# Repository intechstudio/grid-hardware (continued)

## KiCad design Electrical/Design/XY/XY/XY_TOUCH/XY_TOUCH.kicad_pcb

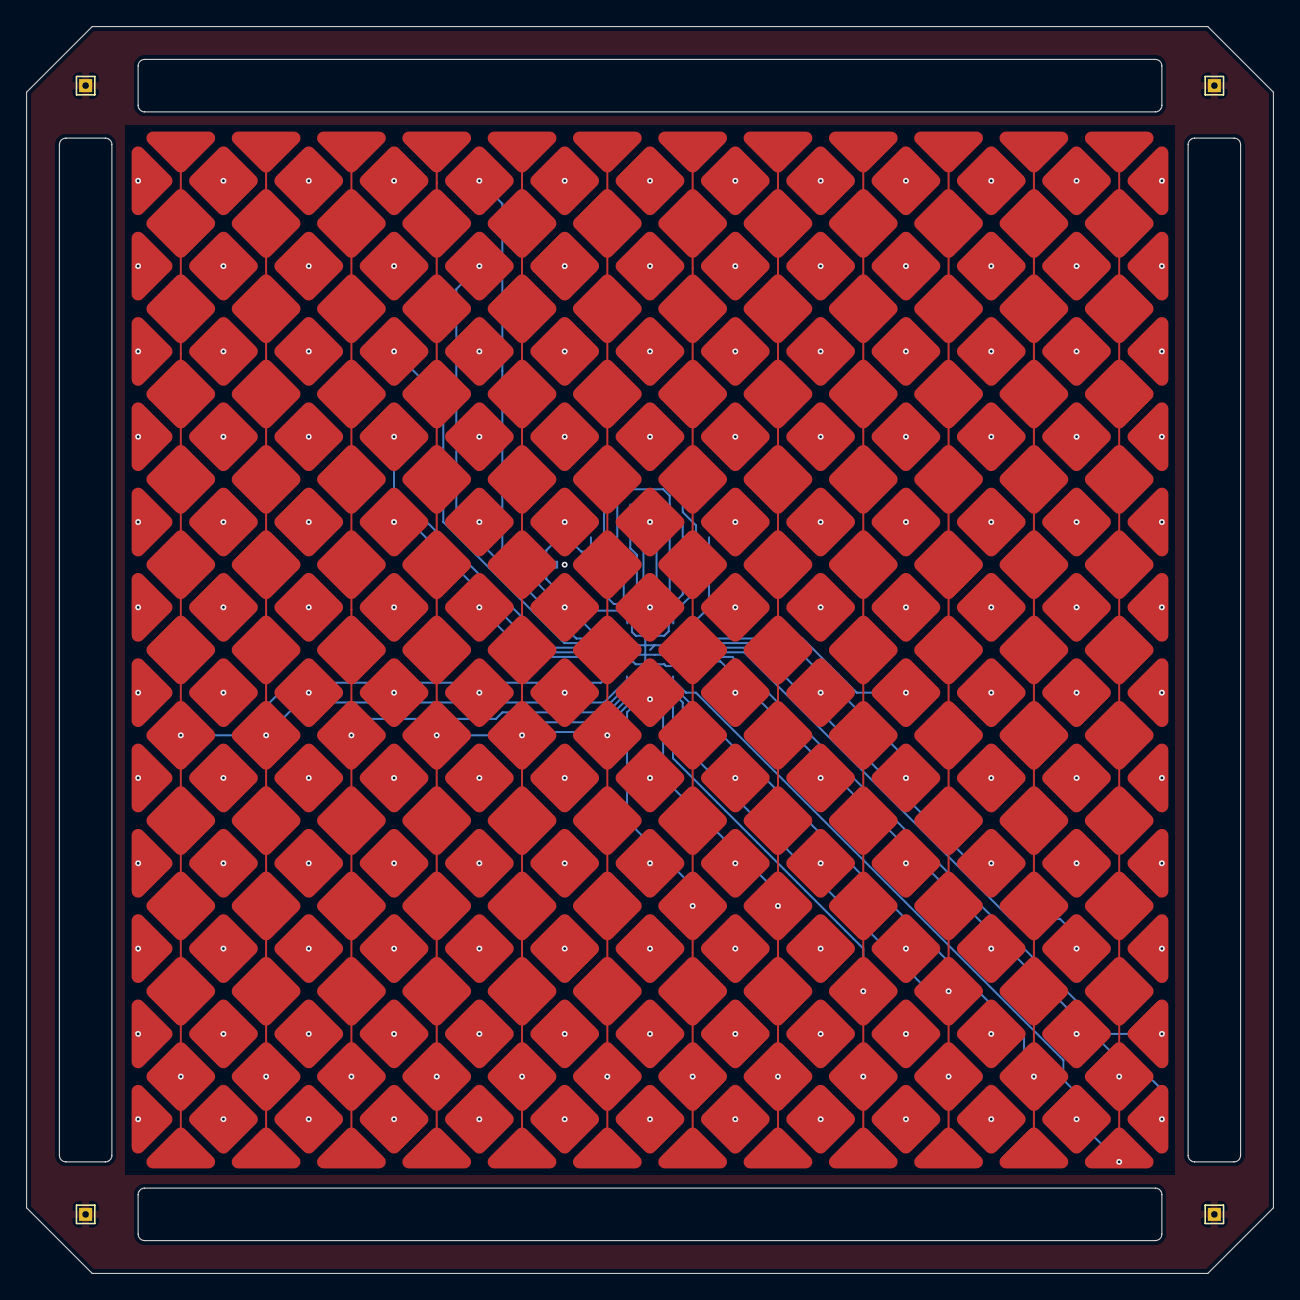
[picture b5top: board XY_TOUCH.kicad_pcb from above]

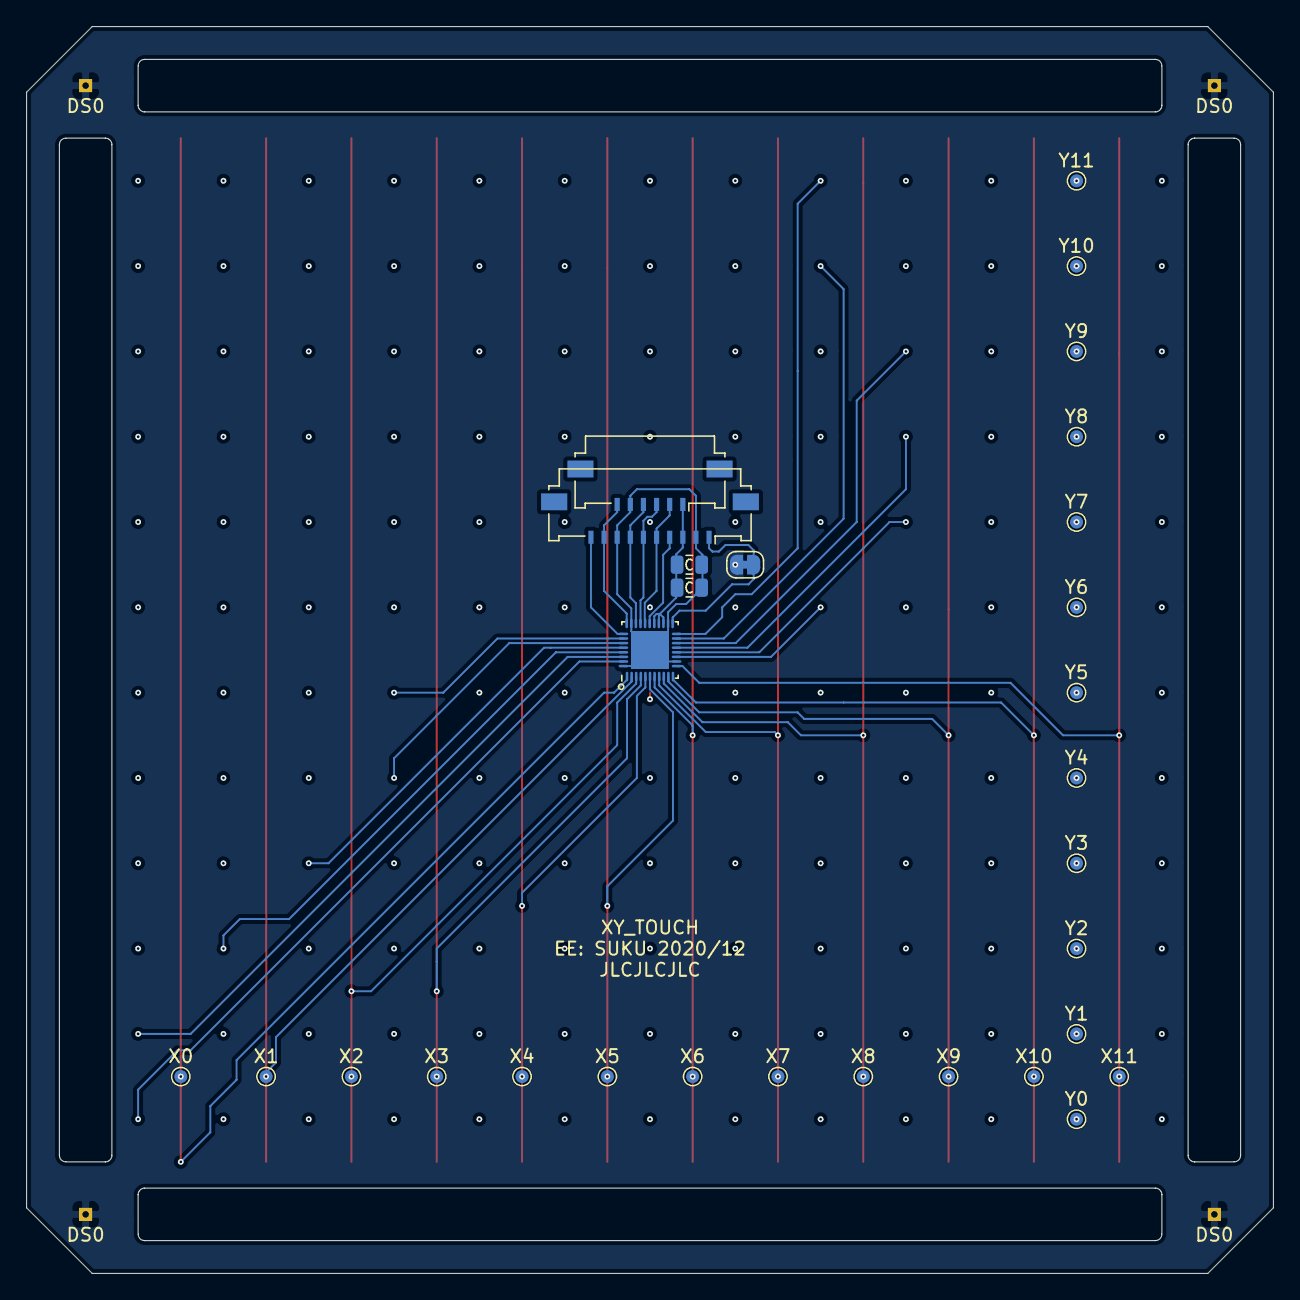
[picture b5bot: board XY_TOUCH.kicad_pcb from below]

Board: 4 copper layers, 95.0 x 95.0 mm, 346 parts (30 on the bottom side), 34 nets.

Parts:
C1: 100n; CAP_0805
C2: 1u; CAP_0805
CS1, CS2, CS3, CS4, CS5, CS6, CS7, CS8, CS9, CS10, CS11, CS12, CS13, CS25, CS38, CS50, CS63, CS75, CS88, CS100, CS113, CS125, CS138, CS150, CS163, CS175, CS188, CS200, CS213, CS225, CS238, CS250, CS263, CS275, CS288, CS300, CS301, CS302, CS303, CS304, CS305, CS306, CS307, CS308, CS309, CS310, CS311, CS312: capsense_diamond_edge
CS14, CS15, CS16, CS17, CS18, CS19, CS20, CS21, CS22, CS23, CS24, CS26, CS27, CS28, CS29, CS30, CS31, CS32, CS33, CS34, CS35, CS36, CS37, CS39, CS40, CS41, CS42, CS43, CS44, CS45, CS46, CS47, CS48, CS49, CS51, CS52, CS53, CS54, CS55, CS56, CS57, CS58, CS59, CS60, CS61, CS62, CS64, CS65, CS66, CS67, CS68, CS69, CS70, CS71, CS72, CS73, CS74, CS76, CS77, CS78, CS79, CS80, CS81, CS82, CS83, CS84, CS85, CS86, CS87, CS89, CS90, CS91, CS92, CS93, CS94, CS95, CS96, CS97, CS98, CS99, CS101, CS102, CS103, CS104, CS105, CS106, CS107, CS108, CS109, CS110, CS111, CS112, CS114, CS115, CS116, CS117, CS118, CS119, CS120, CS121, CS122, CS123, CS124, CS126, CS127, CS128, CS129, CS130, CS131, CS132, CS133, CS134, CS135, CS136, CS137, CS139, CS140, CS141, CS142, CS143, CS144, CS145, CS146, CS147, CS148, CS149, CS151, CS152, CS153, CS154, CS155, CS156, CS157, CS158, CS159, CS160, CS161, CS162, CS164, CS165, CS166, CS167, CS168, CS169, CS170, CS171, CS172, CS173, CS174, CS176, CS177, CS178, CS179, CS180, CS181, CS182, CS183, CS184, CS185, CS186, CS187, CS189, CS190, CS191, CS192, CS193, CS194, CS195, CS196, CS197, CS198, CS199, CS201, CS202, CS203, CS204, CS205, CS206, CS207, CS208, CS209, CS210, CS211, CS212, CS214, CS215, CS216, CS217, CS218, CS219, CS220, CS221, CS222, CS223, CS224, CS226, CS227, CS228, CS229, CS230, CS231, CS232, CS233, CS234, CS235, CS236, CS237, CS239, CS240, CS241, CS242, CS243, CS244, CS245, CS246, CS247, CS248, CS249, CS251, CS252, CS253, CS254, CS255, CS256, CS257, CS258, CS259, CS260, CS261, CS262, CS264, CS265, CS266, CS267, CS268, CS269, CS270, CS271, CS272, CS273, CS274, CS276, CS277, CS278, CS279, CS280, CS281, CS282, CS283, CS284, CS285, CS286, CS287, CS289, CS290, CS291, CS292, CS293, CS294, CS295, CS296, CS297, CS298, CS299: capsense_diamond
J1: Conn_01x06; Molex_200528-0060_1x06-1MP_P1.00mm_Horizontal
J2: Conn_01x10; Molex_200528-0100_1x10-1MP_P1.00mm_Horizontal
JP1: Jumper_2_Bridged; SolderJumper-2_P1.3mm_Bridged_RoundedPad1.0x1.5mm
TP1, TP2, TP3, TP4: DS0; TestPoint_THTPad_1.0x1.0mm_Drill0.5mm
TP5: X11; TestPoint_Pad_D1.0mm
TP6: X10; TestPoint_Pad_D1.0mm
TP7: X9; TestPoint_Pad_D1.0mm
TP8: X8; TestPoint_Pad_D1.0mm
TP9: X7; TestPoint_Pad_D1.0mm
TP10: X6; TestPoint_Pad_D1.0mm
TP11: X5; TestPoint_Pad_D1.0mm
TP12: X4; TestPoint_Pad_D1.0mm
TP13: X3; TestPoint_Pad_D1.0mm
TP14: X2; TestPoint_Pad_D1.0mm
TP15: X1; TestPoint_Pad_D1.0mm
TP16: X0; TestPoint_Pad_D1.0mm
TP17: Y11; TestPoint_Pad_D1.0mm
TP18: Y10; TestPoint_Pad_D1.0mm
TP19: Y9; TestPoint_Pad_D1.0mm
TP20: Y8; TestPoint_Pad_D1.0mm
TP21: Y7; TestPoint_Pad_D1.0mm
TP22: Y6; TestPoint_Pad_D1.0mm
TP23: Y5; TestPoint_Pad_D1.0mm
TP24: Y4; TestPoint_Pad_D1.0mm
TP25: Y3; TestPoint_Pad_D1.0mm
TP26: Y2; TestPoint_Pad_D1.0mm
TP27: Y1; TestPoint_Pad_D1.0mm
TP28: Y0; TestPoint_Pad_D1.0mm
U1: MXT144U; QFN-38_EP_4x4_Pitch0.35mm

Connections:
+3V3_UI: C1.1, C2.1, J1.1, J2.3, U1.22, U1.23, U1.24
/CHG: J1.6, J2.9, U1.30
/DBG_CLK: J2.4, U1.25
/DBG_DATA: J2.1, JP1.2, U1.20
/DBG_SS: J2.10, U1.31
/DS0: JP1.1, TP1.1, TP2.1, TP3.1, TP4.1
/RESET: J1.4, J2.7, U1.28
/SCL: J1.3, J2.6, U1.27
/SDA: J1.2, J2.5, U1.26
/X0: CS288.1, CS289.1, CS290.1, CS291.1, CS292.1, CS293.1, CS294.1, CS295.1, CS296.1, CS297.1, CS298.1, CS299.1, CS300.1, TP16.1, U1.1
/X1: CS263.1, CS264.1, CS265.1, CS266.1, CS267.1, CS268.1, CS269.1, CS270.1, CS271.1, CS272.1, CS273.1, CS274.1, CS275.1, TP15.1, U1.2
/X2: CS238.1, CS239.1, CS240.1, CS241.1, CS242.1, CS243.1, CS244.1, CS245.1, CS246.1, CS247.1, CS248.1, CS249.1, CS250.1, TP14.1, U1.3
/X3: CS213.1, CS214.1, CS215.1, CS216.1, CS217.1, CS218.1, CS219.1, CS220.1, CS221.1, CS222.1, CS223.1, CS224.1, CS225.1, TP13.1, U1.4
/X4: CS188.1, CS189.1, CS190.1, CS191.1, CS192.1, CS193.1, CS194.1, CS195.1, CS196.1, CS197.1, CS198.1, CS199.1, CS200.1, TP12.1, U1.5
/X5: CS163.1, CS164.1, CS165.1, CS166.1, CS167.1, CS168.1, CS169.1, CS170.1, CS171.1, CS172.1, CS173.1, CS174.1, CS175.1, TP11.1, U1.6
/X6: CS138.1, CS139.1, CS140.1, CS141.1, CS142.1, CS143.1, CS144.1, CS145.1, CS146.1, CS147.1, CS148.1, CS149.1, CS150.1, TP10.1, U1.7
/X7: CS113.1, CS114.1, CS115.1, CS116.1, CS117.1, CS118.1, CS119.1, CS120.1, CS121.1, CS122.1, CS123.1, CS124.1, CS125.1, TP9.1, U1.8
/X8: CS88.1, CS89.1, CS90.1, CS91.1, CS92.1, CS93.1, CS94.1, CS95.1, CS96.1, CS97.1, CS98.1, CS99.1, CS100.1, TP8.1, U1.9
/X9: CS63.1, CS64.1, CS65.1, CS66.1, CS67.1, CS68.1, CS69.1, CS70.1, CS71.1, CS72.1, CS73.1, CS74.1, CS75.1, TP7.1, U1.10
/X10: CS38.1, CS39.1, CS40.1, CS41.1, CS42.1, CS43.1, CS44.1, CS45.1, CS46.1, CS47.1, CS48.1, CS49.1, CS50.1, TP6.1, U1.11
/X11: CS13.1, CS14.1, CS15.1, CS16.1, CS17.1, CS18.1, CS19.1, CS20.1, CS21.1, CS22.1, CS23.1, CS24.1, CS25.1, TP5.1, U1.12
/Y0: CS12.1, CS37.1, CS62.1, CS87.1, CS112.1, CS137.1, CS162.1, CS187.1, CS212.1, CS237.1, CS262.1, CS287.1, CS312.1, TP28.1, U1.37
/Y1: CS11.1, CS36.1, CS61.1, CS86.1, CS111.1, CS136.1, CS161.1, CS186.1, CS211.1, CS236.1, CS261.1, CS286.1, CS311.1, TP27.1, U1.36
/Y2: CS10.1, CS35.1, CS60.1, CS85.1, CS110.1, CS135.1, CS160.1, CS185.1, CS210.1, CS235.1, CS260.1, CS285.1, CS310.1, TP26.1, U1.35
/Y3: CS9.1, CS34.1, CS59.1, CS84.1, CS109.1, CS134.1, CS159.1, CS184.1, CS209.1, CS234.1, CS259.1, CS284.1, CS309.1, TP25.1, U1.34
/Y4: CS8.1, CS33.1, CS58.1, CS83.1, CS108.1, CS133.1, CS158.1, CS183.1, CS208.1, CS233.1, CS258.1, CS283.1, CS308.1, TP24.1, U1.33
/Y5: CS7.1, CS32.1, CS57.1, CS82.1, CS107.1, CS132.1, CS157.1, CS182.1, CS207.1, CS232.1, CS257.1, CS282.1, CS307.1, TP23.1, U1.32
/Y6: CS6.1, CS31.1, CS56.1, CS81.1, CS106.1, CS131.1, CS156.1, CS181.1, CS206.1, CS231.1, CS256.1, CS281.1, CS306.1, TP22.1, U1.14
/Y7: CS5.1, CS30.1, CS55.1, CS80.1, CS105.1, CS130.1, CS155.1, CS180.1, CS205.1, CS230.1, CS255.1, CS280.1, CS305.1, TP21.1, U1.15
/Y8: CS4.1, CS29.1, CS54.1, CS79.1, CS104.1, CS129.1, CS154.1, CS179.1, CS204.1, CS229.1, CS254.1, CS279.1, CS304.1, TP20.1, U1.16
/Y9: CS3.1, CS28.1, CS53.1, CS78.1, CS103.1, CS128.1, CS153.1, CS178.1, CS203.1, CS228.1, CS253.1, CS278.1, CS303.1, TP19.1, U1.17
/Y10: CS2.1, CS27.1, CS52.1, CS77.1, CS102.1, CS127.1, CS152.1, CS177.1, CS202.1, CS227.1, CS252.1, CS277.1, CS302.1, TP18.1, U1.18
/Y11: CS1.1, CS26.1, CS51.1, CS76.1, CS101.1, CS126.1, CS151.1, CS176.1, CS201.1, CS226.1, CS251.1, CS276.1, CS301.1, TP17.1, U1.19
GND: C1.2, C2.2, J1.5, J2.2, J2.8, U1.13, U1.21, U1.29, U1.38, U1.39

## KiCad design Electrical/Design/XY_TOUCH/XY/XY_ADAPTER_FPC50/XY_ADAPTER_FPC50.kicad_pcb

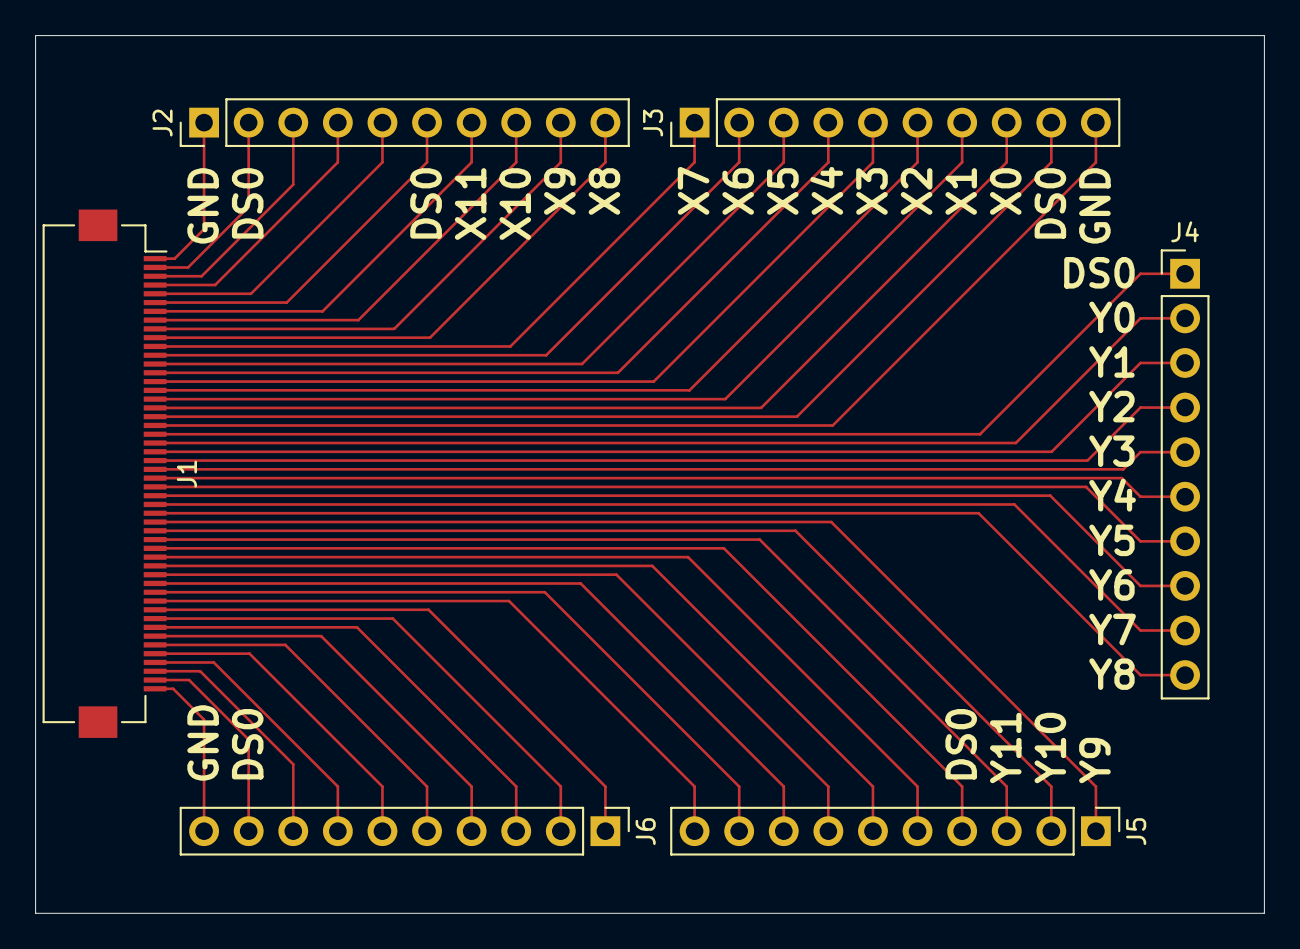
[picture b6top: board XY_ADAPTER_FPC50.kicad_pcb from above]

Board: 2 copper layers, 70.0 x 50.0 mm, 6 parts (0 on the bottom side), 50 nets.

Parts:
J1: Conn_01x50; Hirose_FH12-50S-0.5SH_1x50-1MP_P0.50mm_Horizontal
J2, J3, J4, J5, J6: Conn_01x10; PinHeader_1x10_P2.54mm_Vertical

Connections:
unnamed: J1.1, J2.1
unnamed: J1.2, J2.2
unnamed: J1.3, J2.3
unnamed: J1.4, J2.4
unnamed: J1.5, J2.5
unnamed: J1.6, J2.6
unnamed: J1.7, J2.7
unnamed: J1.8, J2.8
unnamed: J1.9, J2.9
unnamed: J1.10, J2.10
unnamed: J1.11, J3.1
unnamed: J1.12, J3.2
unnamed: J1.13, J3.3
unnamed: J1.14, J3.4
unnamed: J1.15, J3.5
unnamed: J1.16, J3.6
unnamed: J1.17, J3.7
unnamed: J1.18, J3.8
unnamed: J1.19, J3.9
unnamed: J1.20, J3.10
unnamed: J1.21, J4.1
unnamed: J1.22, J4.2
unnamed: J1.23, J4.3
unnamed: J1.24, J4.4
unnamed: J1.25, J4.5
unnamed: J1.26, J4.6
unnamed: J1.27, J4.7
unnamed: J1.28, J4.8
unnamed: J1.29, J4.9
unnamed: J1.30, J4.10
unnamed: J1.31, J5.1
unnamed: J1.32, J5.2
unnamed: J1.33, J5.3
unnamed: J1.34, J5.4
unnamed: J1.35, J5.5
unnamed: J1.36, J5.6
unnamed: J1.37, J5.7
unnamed: J1.38, J5.8
unnamed: J1.39, J5.9
unnamed: J1.40, J5.10
unnamed: J1.41, J6.1
unnamed: J1.42, J6.2
unnamed: J1.43, J6.3
unnamed: J1.44, J6.4
unnamed: J1.45, J6.5
unnamed: J1.46, J6.6
unnamed: J1.47, J6.7
unnamed: J1.48, J6.8
unnamed: J1.49, J6.9
unnamed: J1.50, J6.10
